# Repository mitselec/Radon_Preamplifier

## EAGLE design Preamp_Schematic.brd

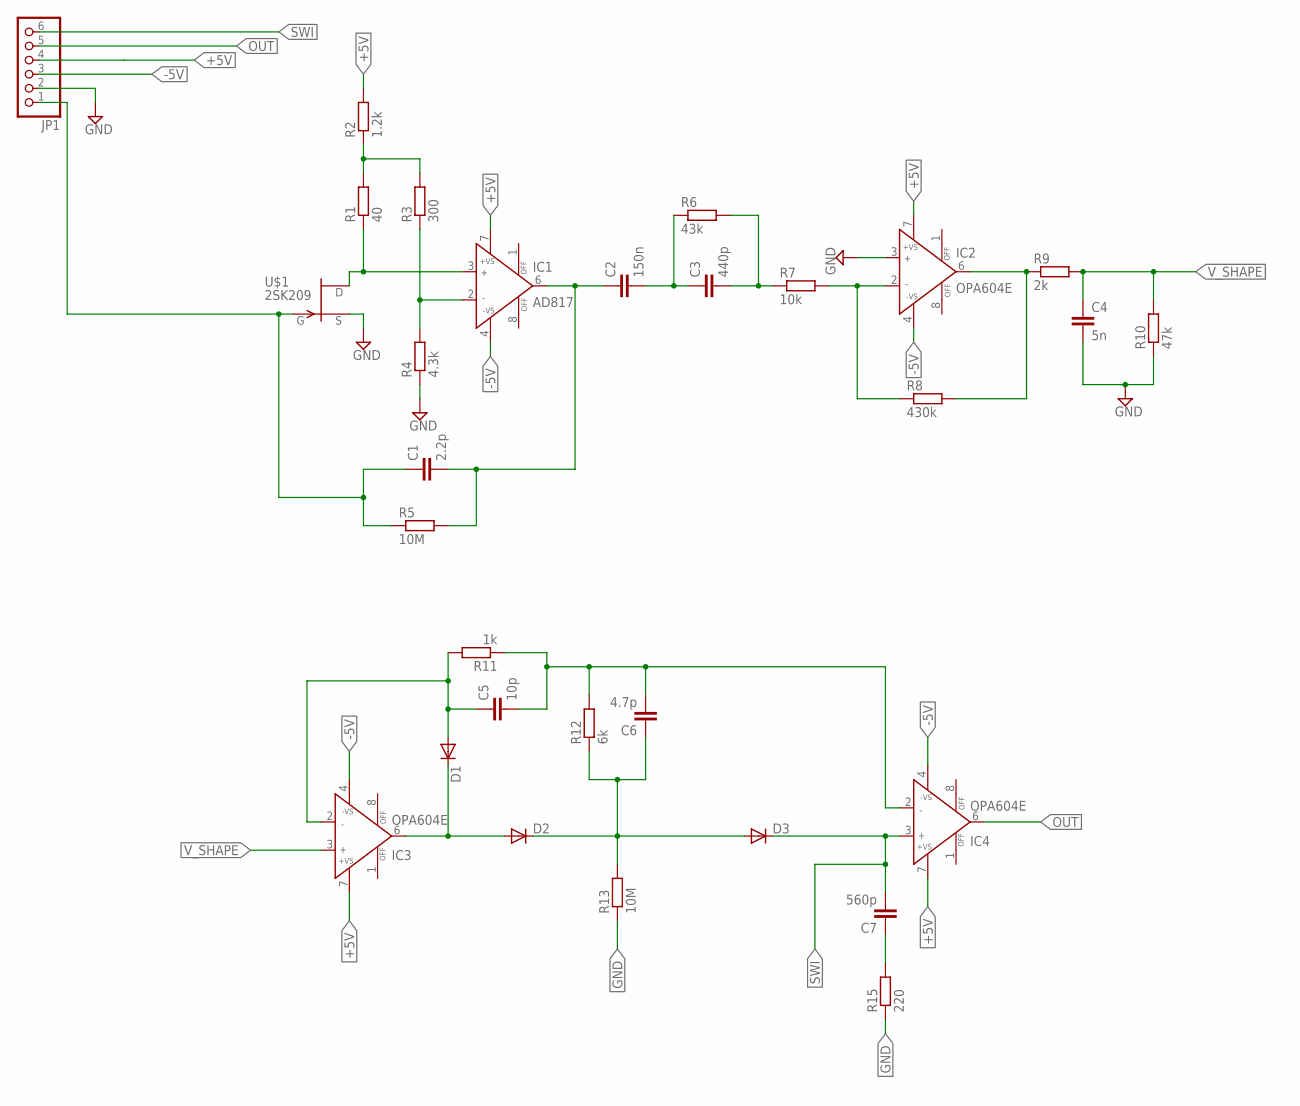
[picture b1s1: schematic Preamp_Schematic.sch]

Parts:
C1: 2.2p; C0805
C2: 150n; C0805
C3: 440p; C0805
C4: 5n; C0805
C5: 10p; C0805
C6: 4.7p; C0805
C7: 560p; C0805
D1, D2, D3: DIODE-SOD123; SOD123
IC1: AD817; SO8
IC2, IC3, IC4: OPA604E; SO8
JP1: PINHD-1X6-3.5MM; 1X06-3.5MM
R1: 40; R0805
R2: 1.2k; R0805
R3: 300; R0805
R4: 4.3k; R0805
R5, R13: 10M; R0805
R6: 43k; R0805
R7: 10k; R0805
R8: 430k; R0805
R9: 2k; R0805
R10: 47k; R0805
R11: 1k; R0805
R12: 6k; R0805
R15: 220; R0805
U$1: 2SK209

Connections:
+5V: IC1.7 (+VS), IC2.7 (+VS), IC3.7 (+VS), IC4.7 (+VS), JP1.4, R2.2
-5V: IC1.4 (-VS), IC2.4 (-VS), IC3.4 (-VS), IC4.4 (-VS), JP1.3
GND: C4.2, IC2.3 (IN+), JP1.2, R4.1, R10.1, R13.1, R15.1, U$1.S
unnamed: C1.2, C2.1, IC1.6 (OUT), R5.2
unnamed: C2.2, C3.1, R6.1
unnamed: C3.2, R6.2, R7.1
unnamed: R1.2, R2.1, R3.2
unnamed: IC2.2 (IN-), R7.2, R8.1
unnamed: IC1.3 (IN+), R1.1, U$1.D
unnamed: IC2.6 (OUT), R8.2, R9.1
unnamed: IC1.2 (IN-), R3.1, R4.2
unnamed: D1.C, D2.A, IC3.6 (OUT)
unnamed: C5.1, D1.A, IC3.2 (IN-), R11.2
unnamed: C5.2, C6.2, IC4.2 (IN-), R11.1, R12.2
unnamed: C6.1, D2.C, D3.A, R12.1, R13.2
unnamed: C7.1, R15.2
OUT: IC4.6 (OUT), JP1.5
SWI: C7.2, D3.C, IC4.3 (IN+), JP1.6
VIN: C1.1, JP1.1, R5.1, U$1.G
V_SHAPE: C4.1, IC3.3 (IN+), R9.2, R10.2

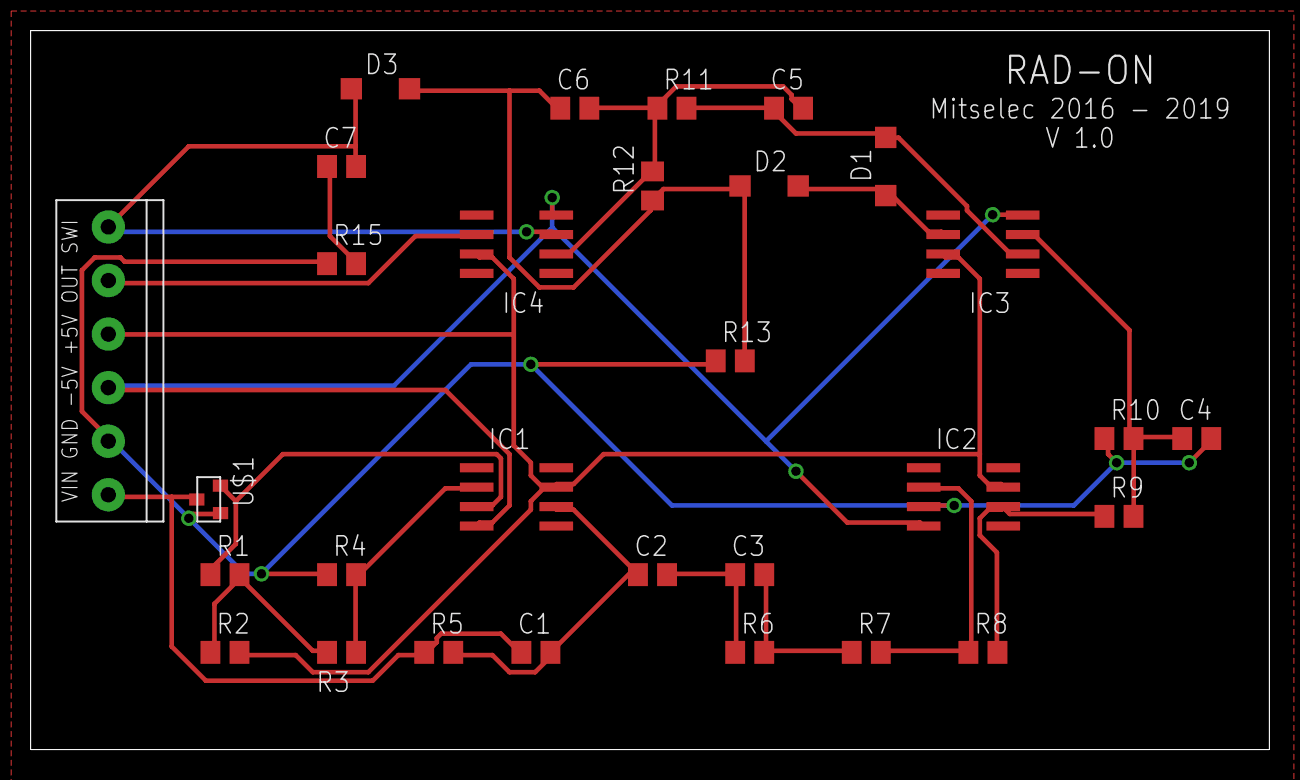
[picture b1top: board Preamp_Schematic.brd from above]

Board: 2 copper layers, 81.0 x 47.0 mm, 30 parts (0 on the bottom side), 20 nets.
